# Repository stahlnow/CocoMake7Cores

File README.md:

# CocoMake7
A jugaad and low-cost educational platform for digital interactivity, compatible with Makey Makey (TM), but based on QTouchADC sensing, local manufacturing and coconuts.
It's based on the ATMEL ATtiny84 and arduino IDE compatible.

There are three different kind of CocoMake7 boards: CocoMake7, KeysCocoMake7 and MIDICocoMake7. The MIDI core is based on the babygnusbuino by a.n.y.m.a.

## Installation

* Download the zip file and unpack it into the hardware folder of your arduino sketchbook folder. The resulting folder structure should be something like ~/your-sketchbook-folder/hardware/MIDICocoMake7Cores-master

* Install the [CocoMake7](https://github.com/CocoMake7/CocoMake7) library.

* For the MIDICocoMake7 you need to install the [MIDICocoMake7](https://github.com/CocoMake7/MIDICocoMake7) library.

## Programming

CocoMake7 boards are programmed via ISP (In-System-Programming).

If you don't have an ISP programmer, you can use an arduino as ISP.

## Pinout
```
// ATMEL ATTINY84 / COCOMAKE7 USB
//
//                   __  __
//            VCC  1|° \/  |14  GND
//   10  XTAL PB0  2|      |13  PA0  A0  0
//    9  XTAL PB1  3|      |12  PA1  A1  1
//       RST  PB3  4|      |11  PA2  A2  2
//   ~8       PB2  5|      |10  PA3  A3  3
//   ~7  USB+ PA7  6|      |9   PA4  A4  4
//   ~6  USB- PA6  7|      |8   PA5  A5  5~
//                   ------
```
## Example sketch

## License

## Contributors

* [dusjagr](https://github.com/dusjagr)
* [stahl](https://github.com/stahlnow)

## Credits

* [mirdej](https://github.com/mirdej)

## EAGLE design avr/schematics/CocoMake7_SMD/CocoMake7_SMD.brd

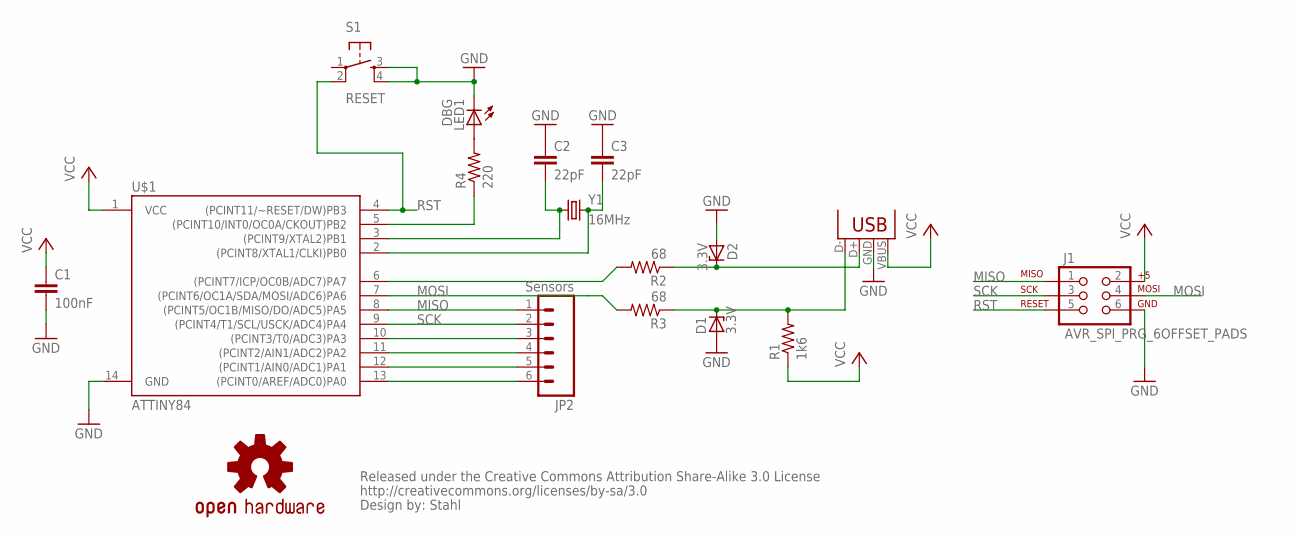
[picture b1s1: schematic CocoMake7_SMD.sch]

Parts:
C1: 100nF; 1206
C2, C3: 22pF; 1206
CC_TEXT1: CREATIVE_COMMONS
D1, D2: 3.3V; SOD80C
J1: AVR_SPI_PRG_6OFFSET_PADS; 2X3_OFFSET
JP1: USB-A-H
JP2: Sensors; 1X06_LONGPADS
LED1: DBG; LED-1206
LOGO1: OSHW-LOGOS; OSHW-LOGO-S
R1: 1k6; 1206
R2, R3: 68; 1206
R4: 220; 1206
S1: RESET; TACTILE_SWITCH_SMD
U$1: ATTINY84; SO14
Y1: 16MHz; HC49UP

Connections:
GND: C1.2, C2.1, C3.1, D1.A, D2.A, J1.6, JP1.GND (VBUS), LED1.C, S1.3, S1.4, U$1.14 (GND)
MISO: J1.1, JP2.1, U$1.8 ((PCINT5/OC1B/MISO/DO/ADC5)PA5)
MOSI: J1.4, R3.2, U$1.7 ((PCINT6/OC1A/SDA/MOSI/ADC6)PA6)
unnamed: D2.C, JP1.D+ (D-), R2.1
unnamed: R2.2, U$1.6 ((PCINT7/ICP/OC0B/ADC7)PA7)
unnamed: C3.2, U$1.2 ((PCINT8/XTAL1/CLKI)PB0), Y1.2
unnamed: JP2.6, U$1.13 ((PCINT0/AREF/ADC0)PA0)
unnamed: C2.2, U$1.3 ((PCINT9/XTAL2)PB1), Y1.1
unnamed: R4.1, U$1.5 ((PCINT10/INT0/OC0A/CKOUT)PB2)
unnamed: LED1.A, R4.2
unnamed: JP2.5, U$1.12 ((PCINT1/AIN0/ADC1)PA1)
unnamed: JP2.4, U$1.11 ((PCINT2/AIN1/ADC2)PA2)
unnamed: JP2.3, U$1.10 ((PCINT3/T0/ADC3)PA3)
unnamed: D1.C, JP1.D- (D+), R1.2, R3.1
RST: J1.5, S1.2, U$1.4 ((PCINT11/~RESET/DW)PB3)
SCK: J1.3, JP2.2, U$1.9 ((PCINT4/T1/SCL/USCK/ADC4)PA4)
VCC: C1.1, J1.2, JP1.VBUS (GND), R1.1, U$1.1 (VCC)

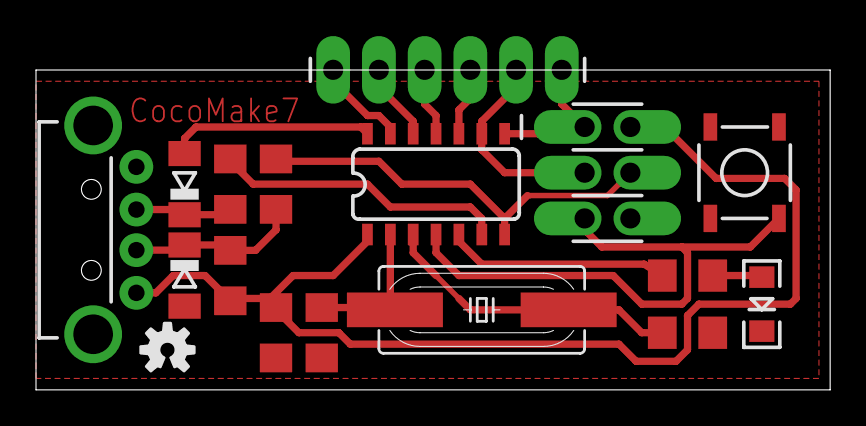
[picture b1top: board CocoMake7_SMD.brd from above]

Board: 2 copper layers, 44.1 x 17.8 mm, 18 parts (0 on the bottom side), 17 nets.

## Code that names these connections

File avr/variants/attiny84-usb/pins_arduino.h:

/*
  pins_arduino.h - Pin definition functions for ATMEGA644
  Part of Arduino - http://www.arduino.cc/

  Copyright (c) 2007 David A. Mellis
  2012 Michael Egger
  2015 Christoph Stähli

  This library is free software; you can redistribute it and/or
  modify it under the terms of the GNU Lesser General Public
  License as published by the Free Software Foundation; either
  version 2.1 of the License, or (at your option) any later version.

  This library is distributed in the hope that it will be useful,
  but WITHOUT ANY WARRANTY; without even the implied warranty of
  MERCHANTABILITY or FITNESS FOR A PARTICULAR PURPOSE.  See the GNU
  Lesser General Public License for more details.

  You should have received a copy of the GNU Lesser General
  Public License along with this library; if not, write to the
  Free Software Foundation, Inc., 59 Temple Place, Suite 330,
  Boston, MA  02111-1307  USA

  $Id: wiring.h 249 2007-02-03 16:52:51Z mellis $
*/

// ATMEL ATTINY84 / COCOMAKE7 USB
//
//                   __  __
//            VCC  1|° \/  |14  GND
//   10  XTAL PB0  2|      |13  PA0  A0  0
//    9  XTAL PB1  3|      |12  PA1  A1  1
//       RST  PB3  4|      |11  PA2  A2  2
//   ~8       PB2  5|      |10  PA3  A3  3
//   ~7  USB+ PA7  6|      |9   PA4  A4  4
//   ~6  USB- PA6  7|      |8   PA5  A5  5~
//                   ------

#ifndef Pins_Arduino_h
#define Pins_Arduino_h

#include <avr/pgmspace.h>

static const uint8_t A0 = 0;
static const uint8_t A1 = 1;
static const uint8_t A2 = 2;
static const uint8_t A3 = 3;
static const uint8_t A4 = 4;
static const uint8_t A5 = 5;
static const uint8_t A6 = 6;
static const uint8_t A7 = 7;


#define digitalPinToPCICR(p)    ( ((p) >= 0 && (p) <= 10) ? (&GIMSK) : ((uint8_t *)0) )
#define digitalPinToPCICRbit(p) ( ((p) <= 7) ? PCIE0 : PCIE1 )
#define digitalPinToPCMSK(p)    ( ((p) <= 7) ? (&PCMSK0) : (((p) <= 10) ? (&PCMSK1) : ((uint8_t *)0)) )
#define digitalPinToPCMSKbit(p) ( ((p) <= 7) ? (p) : (10 - (p)) )


#ifdef ARDUINO_MAIN


const uint16_t PROGMEM port_to_mode_PGM[] = {
	NOT_A_PORT,
    (uint8_t) &DDRA,
	(uint8_t) &DDRB,
};

const uint16_t PROGMEM port_to_output_PGM[] = {
	NOT_A_PORT,
    (uint8_t) &PORTA,
	(uint8_t) &PORTB,
};

const uint16_t PROGMEM port_to_input_PGM[] = {
	NOT_A_PORT,
    (uint8_t) &PINA,
	(uint8_t) &PINB,
};

const uint8_t PROGMEM digital_pin_to_port_PGM[] = {
	// PORTLIST
	// -------------------------------------------
	PA, // 0
    PA,
    PA,
    PA,
    PA,
    PA,
    PA,
    PA,
    PB, // 8
    PB,
    PB,
};

//ok
const uint8_t PROGMEM digital_pin_to_bit_mask_PGM[] = {
	// PIN IN PORT
	// -------------------------------------------
	_BV(0), // port A
    _BV(1),
    _BV(2),
    _BV(3),
    _BV(4),
    _BV(5),
    _BV(6),
    _BV(7),
    _BV(2), // port B
    _BV(1),
    _BV(0),
};

//ok
const uint8_t PROGMEM digital_pin_to_timer_PGM[] = {
	// TIMERS
	// -------------------------------------------
	NOT_ON_TIMER,
    NOT_ON_TIMER,
    NOT_ON_TIMER,
    NOT_ON_TIMER,
    NOT_ON_TIMER,
    TIMER1B, // OC1B
    TIMER1A, // OC1A
    TIMER0B, // OC0B
    TIMER0A, // OC0A
    NOT_ON_TIMER,
    NOT_ON_TIMER,
};

#endif

#endif

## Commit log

2015-05-22 fix paths
2015-05-22 arduino isp programming
2015-05-22 fix image
2015-05-22 added usb variant
2015-05-22 updated pwm pins
2015-05-22 fixed include paths for midicocomake7 library
2015-05-22 added variants and clock menu
2015-05-22 updated pin mapping functions
2015-05-22 removed compiler path
2015-05-22 fixed mappings
2015-05-22 update install instructions
2015-05-22 fix install instructions
2015-05-24 updated usb d+ and d- pins
2015-05-24 added pinout
2015-06-19 added device check
2015-06-19 ignore eagle tempoorary files and eps
2015-06-19 added schematics
2015-06-24 ignore eagle pro and epf files
2015-06-24 removed pro and epf files
2015-12-16 added keyboard core

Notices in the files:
parts and their libraries:
SparkFun-Capacitors: Licensing: CC v3.0 Share-Alike You are welcome to use this library for commercial purposes.
SparkFun-Aesthetics: Released under the Creative Commons Attribution Share-Alike 3.0 License
SparkFun-Aesthetics: http://creativecommons.org/licenses/by-sa/3.0
